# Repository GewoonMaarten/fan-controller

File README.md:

# PWM Fan Controller
Arduino fan controller with schematic and pcb. The goal of the project is to create a fan controller that uses a potentiometer as means of controller and a screen as visual output to controller a fan.
In my case I use it to control the fan on my 3D printer, the Cetus3D MKIII.

The PCB was specificly designed for the Cetus3D 3D printer.

# Libraries
- [Adafruit_SH1106](https://github.com/wonho-maker/Adafruit_SH1106). I use the SH1106 as screen, however you can easily change the code to use any other OLED screen.
- [Adafruit-GFX-Library](https://github.com/adafruit/Adafruit-GFX-Library). You can also get this from the Arduino library manager.

# Acknowledgements
- Thanks to [wonho-maker](https://github.com/wonho-maker) for the SH1106 library.
- Thanks to [Adafruit](https://www.adafruit.com/) for creating the GFX library.

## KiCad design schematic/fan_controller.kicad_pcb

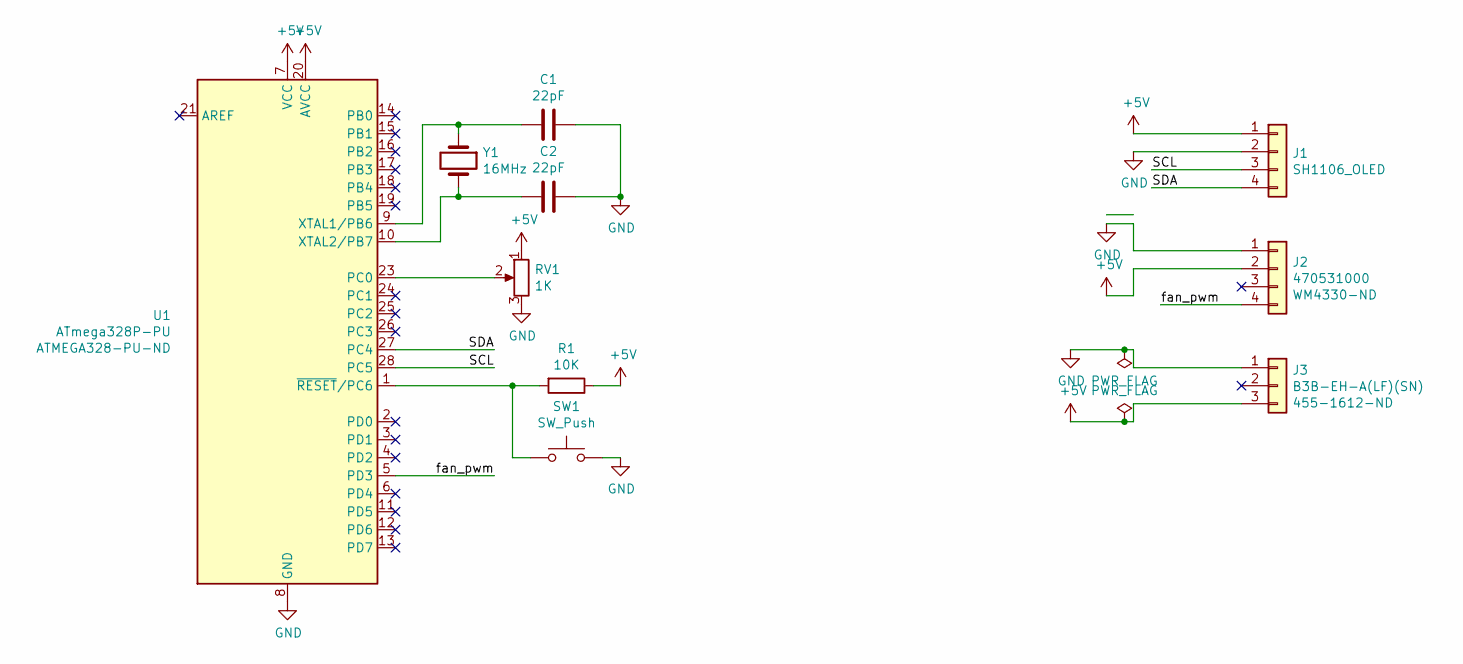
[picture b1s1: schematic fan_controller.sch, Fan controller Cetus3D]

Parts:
C1, C2: 22pF; C_Disc_D5.0mm_W2.5mm_P5.00mm
J1: SH1106_OLED; PinHeader_1x04_P2.54mm_Horizontal
J2: 470531000; digikey WM4330-ND
J3: B3B-EH-A(LF)(SN); JST_EH_B3B-EH-A_1x03_P2.50mm_Vertical
R1: 10K; R_Axial_DIN0207_L6.3mm_D2.5mm_P7.62mm_Horizontal
RV1: 1K; Potentiometer_Piher_T-16H_Single_Horizontal
SW1: SW_Push; SW_PUSH_6mm
U1: ATmega328P-PU; DIP-28_W7.62mm; digikey ATMEGA328-PU-ND
Y1: 16MHz; Crystal_HC49-4H_Vertical

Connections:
+5V: J1.1, J2.2, J3.3, R1.1, RV1.1, U1.7 (VCC), U1.20 (AVCC)
/SCL: J1.3, U1.28 (PC5)
/SDA: J1.4, U1.27 (PC4)
/fan_pwm: J2.4, U1.5 (PD3)
GND: C1.1, C2.1, J1.2, J2.1, J3.1, RV1.3, SW1.2, U1.8 (GND), U1.22 (GND)
unnamed: C1.2, U1.9 (XTAL1/PB6), Y1.1
unnamed: C2.2, U1.10 (XTAL2/PB7), Y1.2
unnamed: R1.2, SW1.1, U1.1 (~RESET~/PC6)
unnamed: RV1.2, U1.23 (PC0)

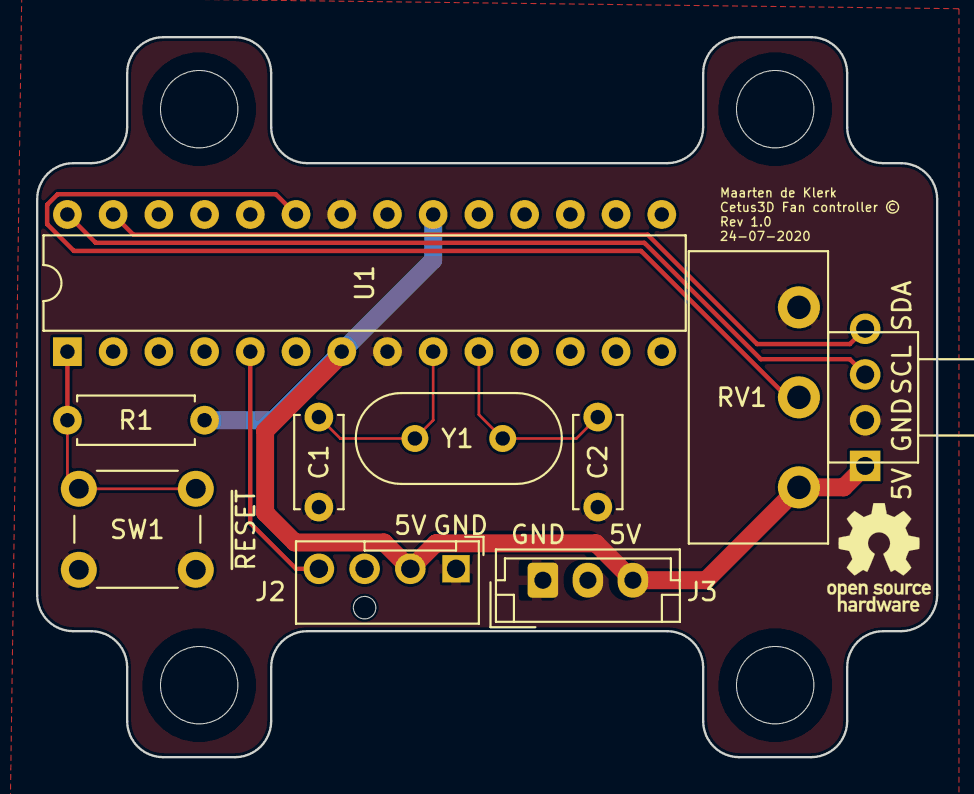
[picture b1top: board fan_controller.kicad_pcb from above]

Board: 2 copper layers, 50.0 x 40.0 mm, 10 parts (1 on the bottom side), 9 nets.

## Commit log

2020-07-25 Added files
2020-07-25 Added schematic as pdf
2020-07-30 Added smoothing to potentiometer input
    As I forgot it on the hardware.
2020-07-30 Updated schematic
2020-07-31 renamed folder
2020-07-31 Added images
2020-07-31 Added images to readme
